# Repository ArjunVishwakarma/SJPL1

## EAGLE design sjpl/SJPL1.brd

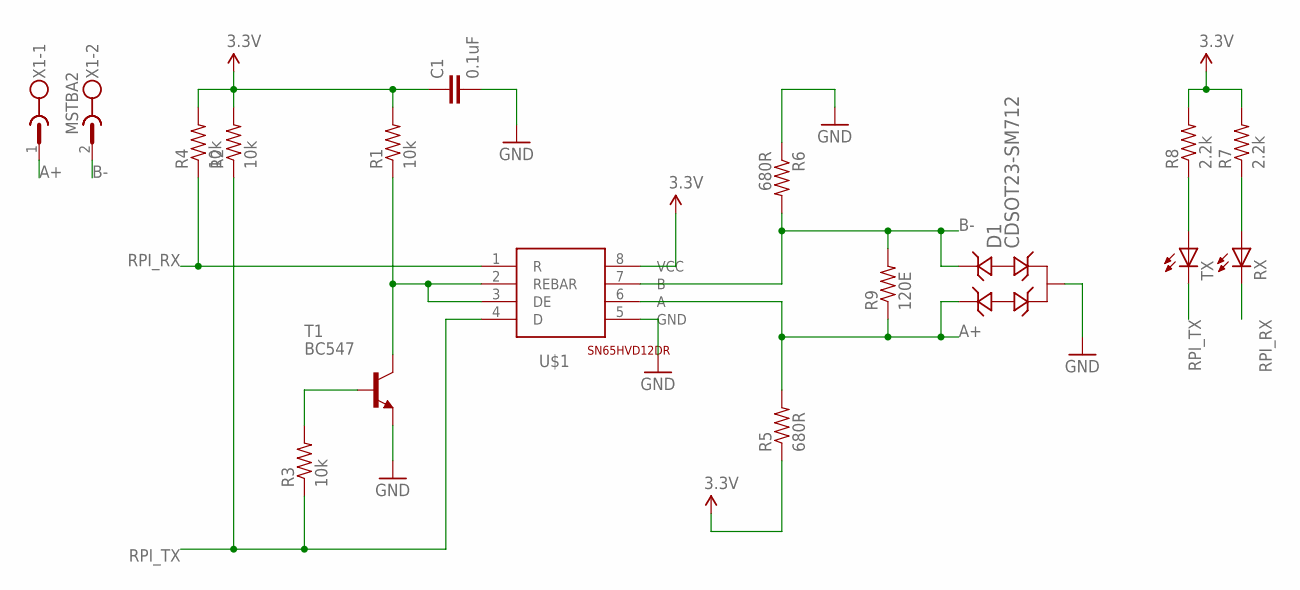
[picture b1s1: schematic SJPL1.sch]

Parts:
C1: 0.1uF; 0402-CAP
D1: CDSOT23-SM712; SOT-23-3
R1, R2, R3, R4: 10k; 0402-RES
R5, R6: 680R; 0402-RES
R7, R8: 2.2k; 0402-RES
R9: 120E; 0402-RES
RX: LED5MM
T1: BC547; TO92
TX: LED5MM
U$1: MODBUS-DIP8MODBUSSO; MODBUSS0
X1: MSTBA2

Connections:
A+: D1.1 (IO1), R5.2, R9.1, X1.1
B-: D1.2 (IO2), R6.2, R9.2, X1.2
GND: C1.2, D1.3 (GND), R6.1
unnamed: R8.1, TX.A
unnamed: R7.1, RX.A
unnamed: R1.1, T1.3 (C), U$1.2 (REBAR), U$1.3 (DE)
unnamed: R3.2, T1.2 (B)
RPI_RX: R4.1, RX.K (C), U$1.1 (R)
RPI_TX: R2.1, R3.1, TX.K (C), U$1.4 (D)
VCC: C1.1, R1.2, R2.2, R4.2, R5.1, R7.2, R8.2

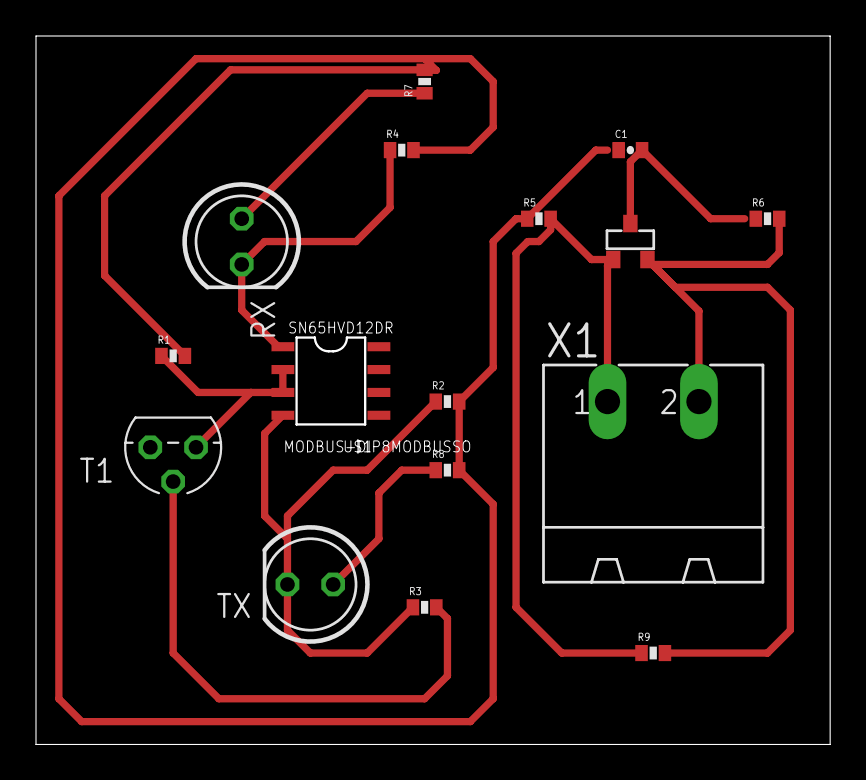
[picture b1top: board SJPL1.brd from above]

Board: 2 copper layers, 44.0 x 39.2 mm, 16 parts (0 on the bottom side), 10 nets.

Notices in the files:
parts and their libraries:
SparkFun-Passives: Licensing: Creative Commons ShareAlike 4.0 International - https://creativecommons.org/licenses/by-sa/4.0
